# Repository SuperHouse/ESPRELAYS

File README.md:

ESPRELAYS: ESP8266 Reed Relay Board
====================================

Copyright 2017-2019 SuperHouse Automation Pty Ltd  www.superhouse.tv  

Allows an appliance remote control to be connected to an ESP8266 so that it
can be triggered remotely as if the buttons were pushed.

Features:

 * ESP8266 MCU with wifi.
 * 6 dry-contact reed relay outputs.
 * Headers for GND, 3.3V, and 5V to power the remote control.
 * 2.1mm DC jack for 7-24Vdc power input.
 * Efficient 5V switchmode power supply with 3.3V linear regulator.

More information is available at:

  http://www.superhouse.tv/esprelays

INSTALLATION
------------
The design is saved as an EAGLE project. EAGLE PCB design software is
available from www.cadsoftusa.com free for non-commercial use. To use
this project download it and place the directory containing these files
into the "eagle" directory on your computer.

DISTRIBUTION
------------
The specific terms of distribution of this project are governed by the
license referenced below.

LICENSE
-------
Licensed under the TAPR Open Hardware License (www.tapr.org/OHL).
The "license" folder within this repository also contains a copy of
this license in plain text format.

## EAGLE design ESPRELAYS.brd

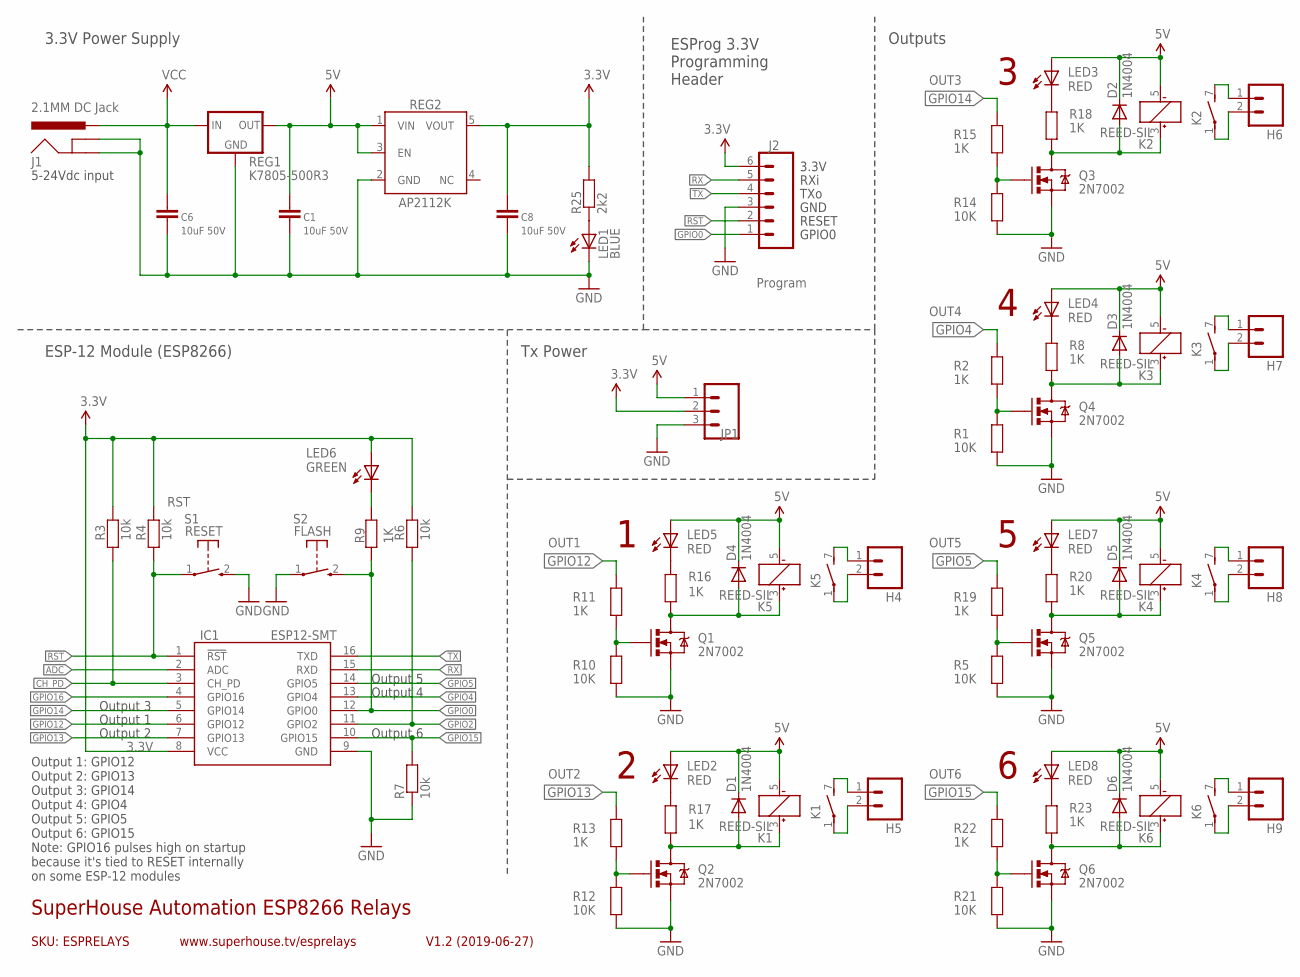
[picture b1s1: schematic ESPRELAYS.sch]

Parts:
C1, C6, C8: 10uF 50V; C0805
D1, D2, D3, D4, D5, D6: 1N4004; SMA-DIODE
H4, H5, H6, H7, H8, H9: M02-PIN; 1X02-P
IC1: ESP12-SMT; ESP12
J1: 2.1MM DC Jack; POWER_JACK_SLOTS
J2: Program; 1X06-S
JP1: M03-PLAIN; 1X03
K1, K2, K3, K4, K5, K6: REED-SIL; REED
LED1: BLUE; LED-0603
LED2, LED3, LED4, LED5, LED7, LED8: RED; LED-0603
LED6: GREEN; LED-0603
Q1, Q2, Q3, Q4, Q5, Q6: 2N7002; SOT23-3
R1, R5, R10, R12, R14, R21: 10K; R0603
R2, R8, R9, R11, R13, R15, R16, R17, R18, R19, R20, R22, R23: 1K; R0603
R3, R4, R6, R7: 10k; R0603
R25: 2k2; R0603
REG1: K7805-500R3; K78XX-500R3
REG2: AP2112KSOT25; SOT23-5
S1: RESET; TACTILE_SMD_3X4X2
S2: FLASH; TACTILE_SMD_3X4X2

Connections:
3.3V: C8.1, IC1.8 (VCC), J2.6, JP1.2, LED6.A, R3.2, R4.2, R6.2, R25.2, REG2.5 (VOUT)
5V: C1.1, D1.C, D2.C, D3.C, D4.C, D5.C, D6.C, JP1.1, K1.5 (-), K2.5 (-), K3.5 (-), K4.5 (-), K5.5 (-), K6.5 (-), LED2.A, LED3.A, LED4.A, LED5.A, LED7.A, LED8.A, REG1.3 (OUT), REG2.1 (VIN), REG2.3 (EN)
ADC: IC1.2 (ADC)
CH_PD: IC1.3 (CH_PD), R3.1
GND: C1.2, C6.2, C8.2, IC1.9 (GND), J1.GND, J1.GNDBREAK, J2.3, JP1.3, LED1.C, Q1.2 (S), Q2.2 (S), Q3.2 (S), Q4.2 (S), Q5.2 (S), Q6.2 (S), R1.1, R5.1, R7.1, R10.1, R12.1, R14.1, R21.1, REG1.2 (GND), REG2.2 (GND), S1.2 (S), S2.1
GPIO0: IC1.12 (GPIO0), J2.1, R9.2, S2.2 (S)
GPIO2: IC1.11 (GPIO2), R6.1
GPIO4: IC1.13 (GPIO4), R2.2
GPIO5: IC1.14 (GPIO5), R19.2
GPIO12: IC1.6 (GPIO12), R11.2
GPIO13: IC1.7 (GPIO13), R13.2
GPIO14: IC1.5 (GPIO14), R15.2
GPIO15: IC1.10 (GPIO15), R7.2, R22.2
GPIO16: IC1.4 (GPIO16)
unnamed: Q1.1 (G), R10.2, R11.1
unnamed: Q2.1 (G), R12.2, R13.1
unnamed: H5.1, K1.7 (S)
unnamed: LED3.C, R18.1
unnamed: H5.2, K1.1
unnamed: H6.1, K2.7 (S)
unnamed: Q4.1 (G), R1.2, R2.1
unnamed: H4.1, K5.7 (S)
unnamed: H6.2, K2.1
unnamed: Q3.1 (G), R14.2, R15.1
unnamed: LED4.C, R8.1
unnamed: H4.2, K5.1
unnamed: H7.1, K3.7 (S)
unnamed: H7.2, K3.1
unnamed: H8.1, K4.7 (S)
unnamed: H8.2, K4.1
unnamed: H9.1, K6.7 (S)
unnamed: H9.2, K6.1
unnamed: Q5.1 (G), R5.2, R19.1
unnamed: LED7.C, R20.1
unnamed: LED2.C, R17.1
unnamed: Q6.1 (G), R21.2, R22.1
unnamed: LED1.A, R25.1
unnamed: LED5.C, R16.1
unnamed: LED8.C, R23.1
unnamed: LED6.C, R9.1
OUT1: D4.A, K5.3 (+), Q1.3 (D), R16.2
OUT2: D1.A, K1.3 (+), Q2.3 (D), R17.2
OUT3: D2.A, K2.3 (+), Q3.3 (D), R18.2
OUT4: D3.A, K3.3 (+), Q4.3 (D), R8.2
OUT5: D5.A, K4.3 (+), Q5.3 (D), R20.2
OUT6: D6.A, K6.3 (+), Q6.3 (D), R23.2
RST: IC1.1 (!RST), J2.2, R4.1, S1.1
RX: IC1.15 (RXD), J2.5
TX: IC1.16 (TXD), J2.4
VCC: C6.1, J1.PWR, REG1.1 (IN)

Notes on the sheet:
SKU: ESPRELAYS
SuperHouse Automation ESP8266 Relays
V1.2 (2019-06-27)
www.superhouse.tv/esprelays
3.3V Power Supply
Outputs
ESP-12 Module (ESP8266)
ESProg 3.3V Programming Header
5-24Vdc input
Output 1: GPIO12 Output 2: GPIO13 Output 3: GPIO14 Output 4: GPIO4 Output 5: GPIO5 Output 6: GPIO15 Note: GPIO16 pulses high on startup because it's tied to RESET internally on some ESP-12 modules
Output 1
Output 2
Output 3
Output 4
Output 5
Output 6
Tx Power
3.3V
RXi
TXo
GND
RESET
GPIO0

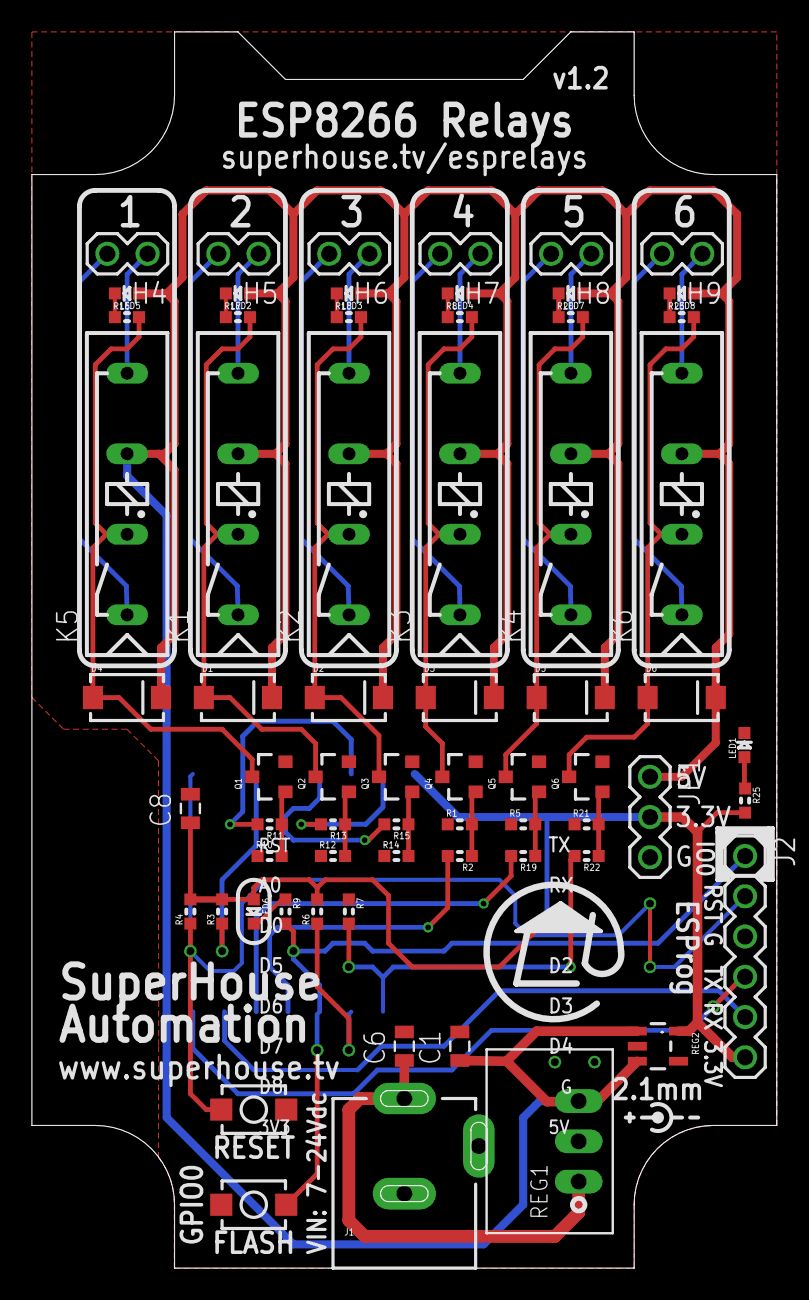
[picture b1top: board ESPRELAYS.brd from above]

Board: 2 copper layers, 47.0 x 78.0 mm, 67 parts (1 on the bottom side), 48 nets.

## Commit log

2019-02-19 Added reed relays
2019-02-19 Renamed project files
2019-02-19 Added SIP reed relays
2019-04-11 Routing for v1.0 release
2019-04-17 Improved value designators
2019-04-26 Changed output pins to avoid GPIO16 because it pulses on startup. v1.1 release
2019-06-01 Fixed revision number in schematic
2019-07-01 Replaced most parts using SuperHouse library to add 3D models

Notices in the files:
ESPRELAYS.brd:
(C)2019 SuperHouse
Hardware Licence: tapr.org/ohl
parts and their libraries:
freetronics-original: Licensing: CC v3.0 Share-Alike You are welcome to use this library for commercial purposes.
